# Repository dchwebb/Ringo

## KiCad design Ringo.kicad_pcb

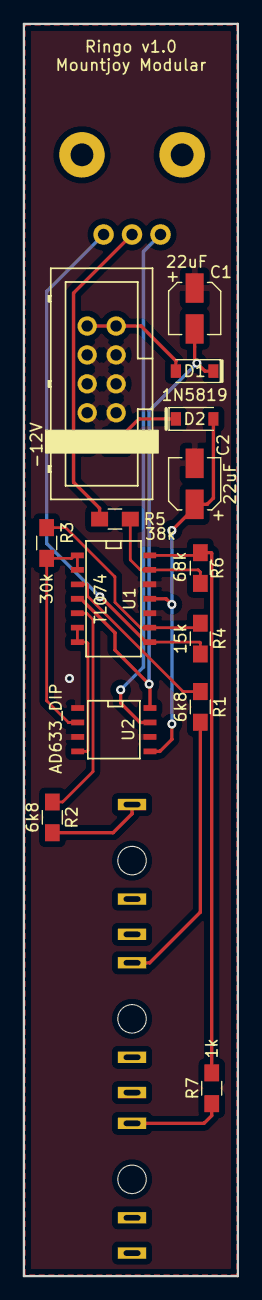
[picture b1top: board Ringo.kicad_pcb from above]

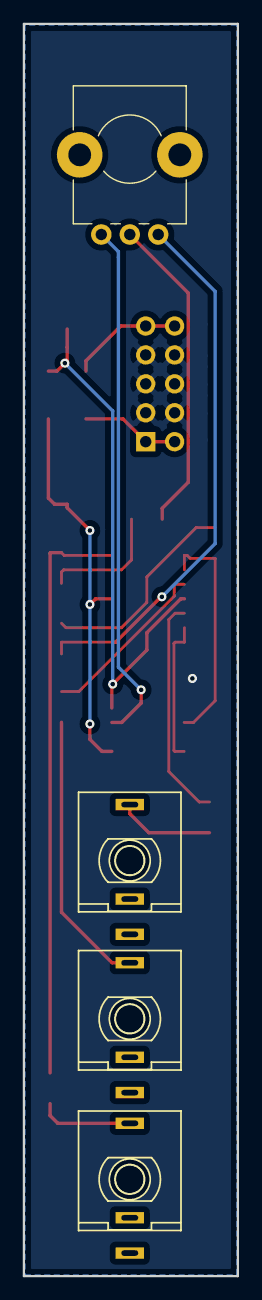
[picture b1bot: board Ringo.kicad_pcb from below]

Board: 2 copper layers, 18.8 x 110.0 mm, 18 parts (4 on the bottom side), 18 nets.

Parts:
C1, C2: 22uF; CP_Elec_4x5.8
D1, D2: 1N5819; D_SOD-123
J1: Modulator_Input; THONKICONN_hole
J2: Carrier_Input; THONKICONN_hole
J3: Eurorack_10_pin_power; Eurorack_10_pin_header
J4: Output; THONKICONN_hole
R1, R2: 6k8; R_0805_HandSoldering
R3: 30k; R_0805_HandSoldering
R4: 15k; R_0805_HandSoldering
R5: 38k; R_0805_HandSoldering
R6: 68k; R_0805_HandSoldering
R7: 1k; R_0805_HandSoldering
RV1: 10k; Alpha_9mm_Potentiometer
U1: TL074; SOIC-14_N
U2: AD633_DIP; SOIC-8-N

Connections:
+12V: D1.2, J3.9, J3.10
-12V: D2.1, J3.1, J3.2
GND: C1.1, C2.2, J3.3, J3.4, J3.5, J3.6, J3.7, J3.8, U1.10, U1.12, U2.1, U2.3, U2.6
unnamed: J1.3, R1.2
unnamed: J2.3, R2.2
unnamed: J4.3, R7.1
unnamed: R1.1, U1.3
unnamed: R2.1, U1.5
unnamed: R3.1, R4.1, U1.9
unnamed: R3.2, U1.1, U1.2, U2.2
unnamed: R4.2, RV1.1, U1.8
unnamed: R5.1, R6.1, U1.13
unnamed: R5.2, RV1.2
unnamed: R6.2, R7.2, U1.14
unnamed: RV1.3, U2.7
unnamed: U1.6, U1.7, U2.4
VCC: C1.2, D1.1, U1.4, U2.8
VEE: C2.1, D2.2, U1.11, U2.5

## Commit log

2021-09-23 Updated to tested working schematic
2021-09-23 Fixed naming to Ringo
